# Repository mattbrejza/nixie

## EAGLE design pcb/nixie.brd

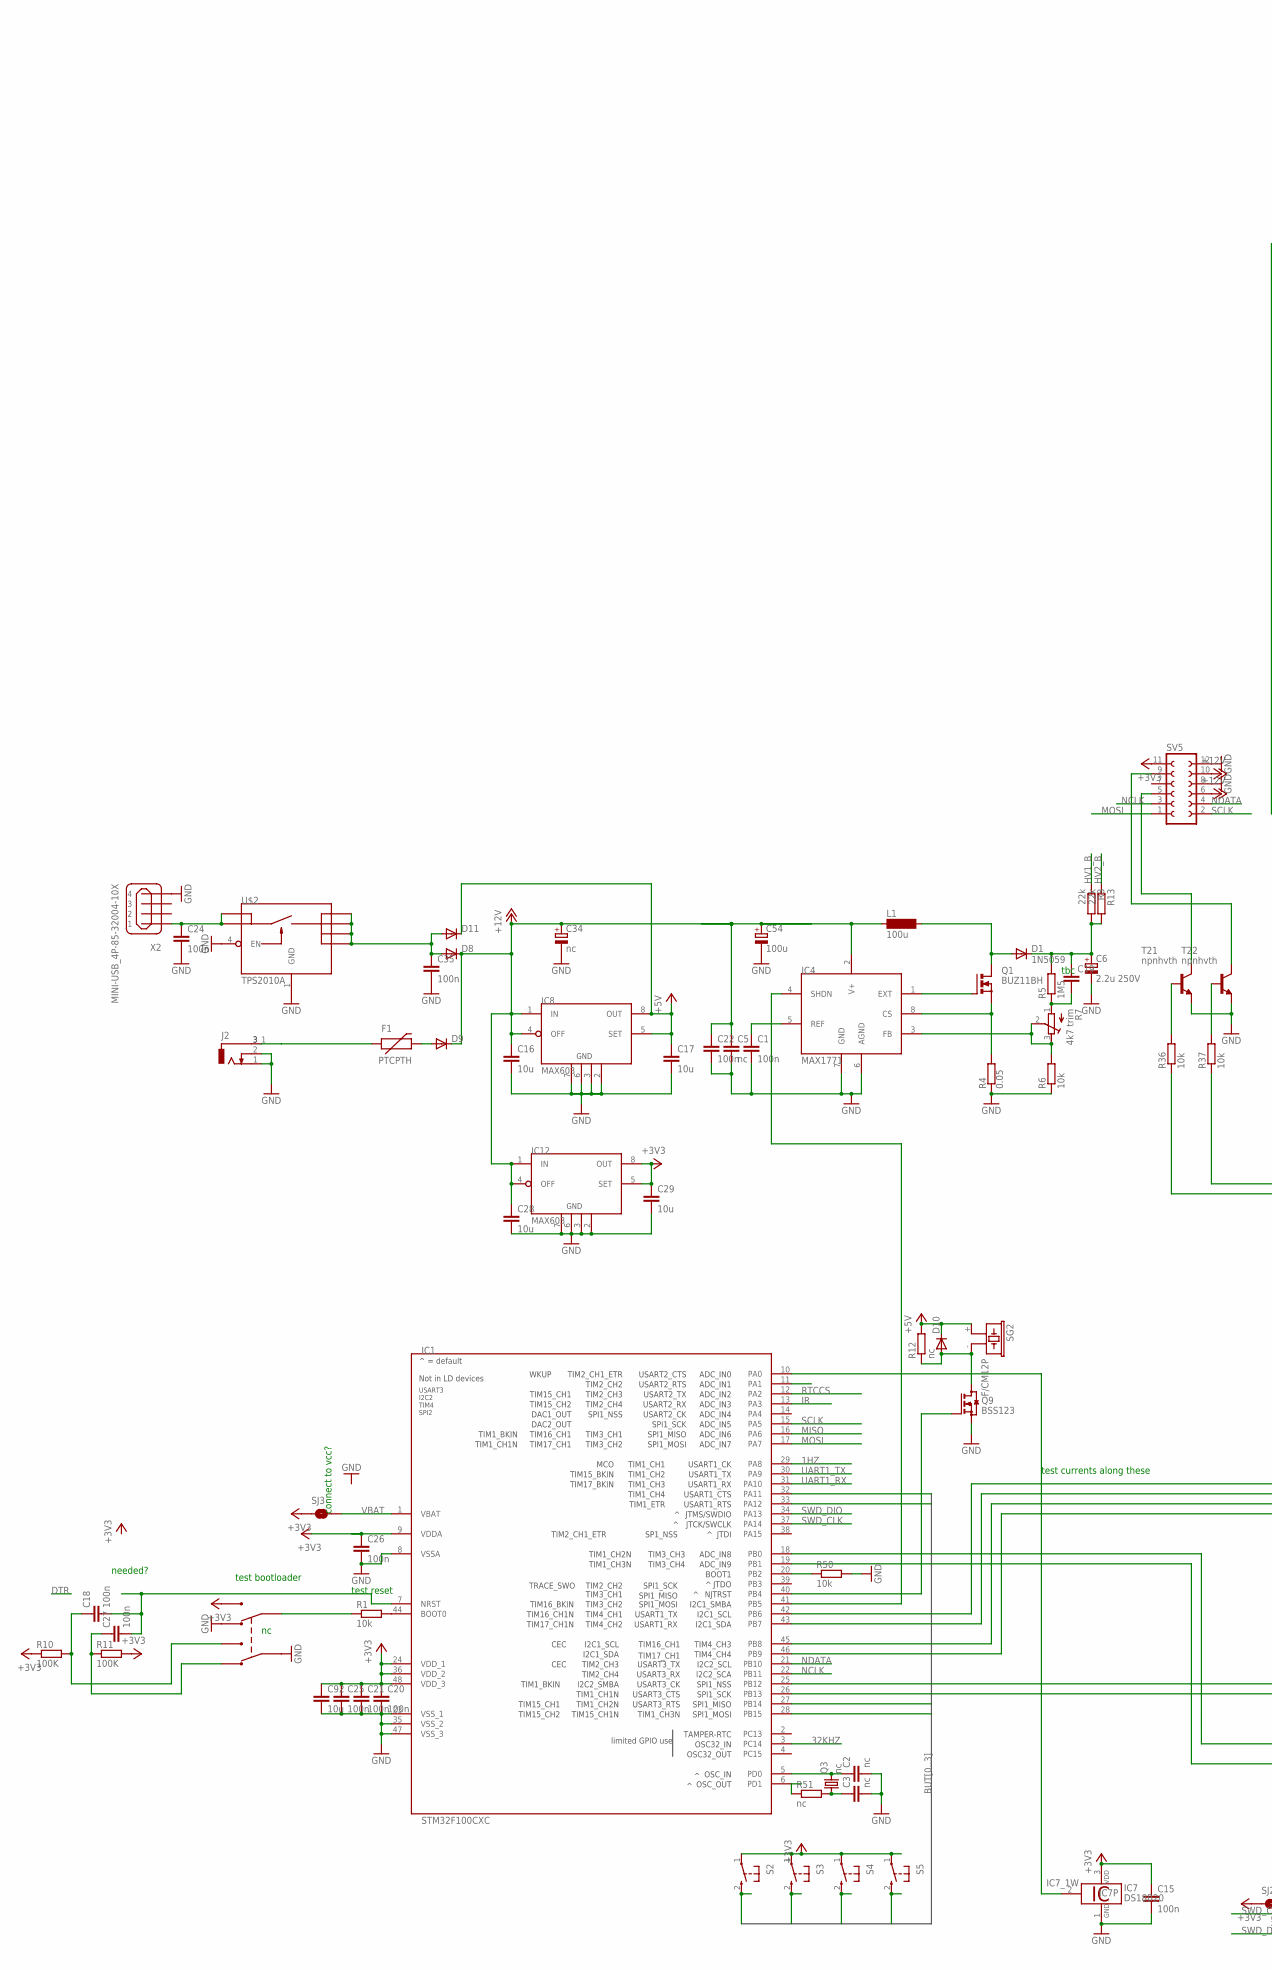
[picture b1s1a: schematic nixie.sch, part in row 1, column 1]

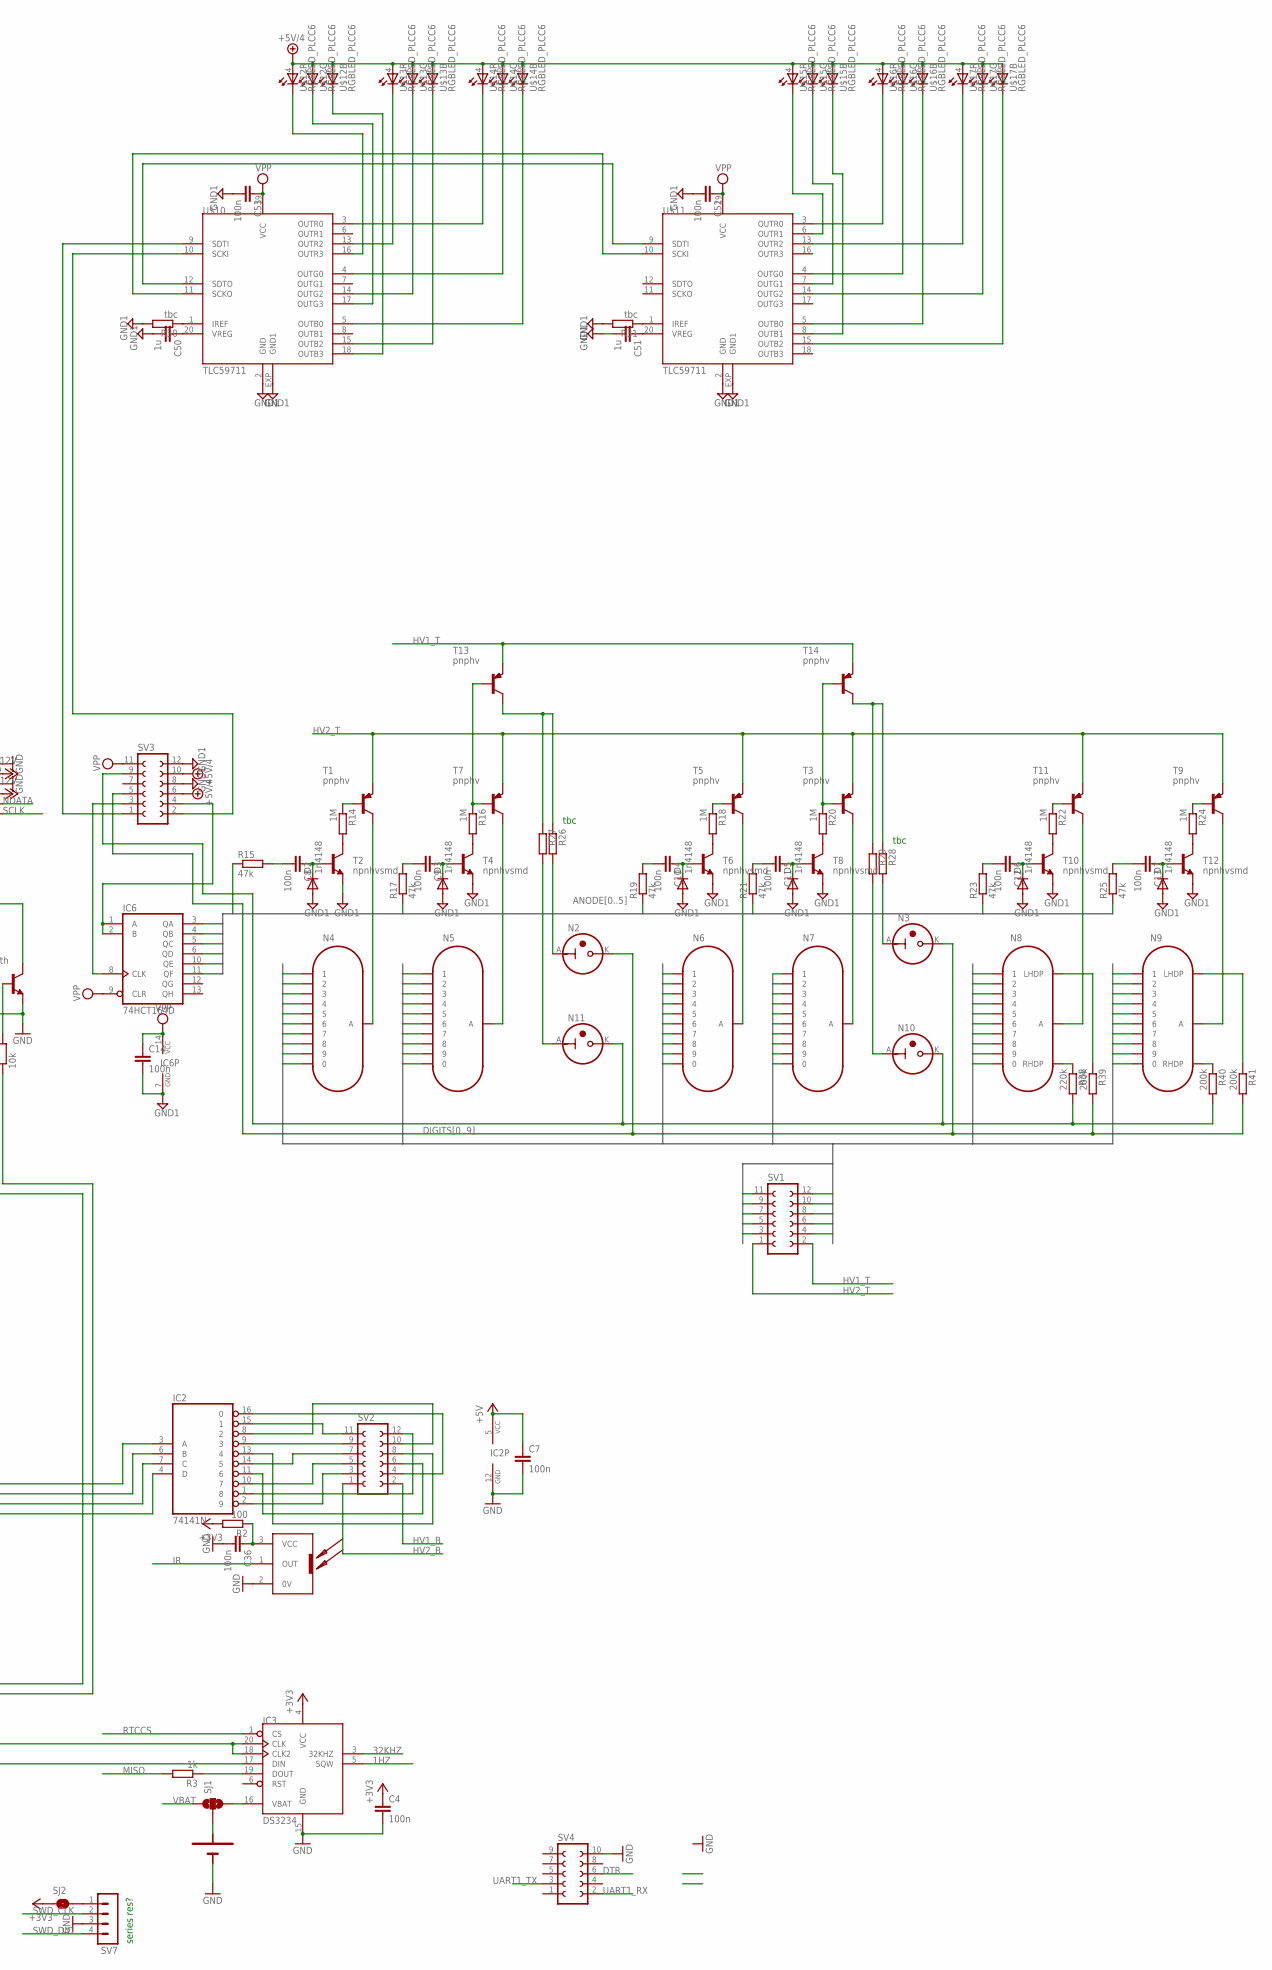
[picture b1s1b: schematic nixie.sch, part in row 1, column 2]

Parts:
BAT1: 2032; COIN
C1, C4, C7, C8, C9, C10, C11, C12, C13, C14, C15, C18, C20, C21, C22, C24, C25, C26, C27, C35, C36, C52, C53: 100n; C0603
C2, C3, C5: nc; C0603
C6: 2.2u 250V; E2,5-6
C16, C17, C28, C29, C92: 10u; C0603
C19: C-EUC0603; C0603
C34: nc; SMC_C
C50, C51: 1u; C0603
C54: 100u; E2,5-6
D1: 1N5059; C1702-05
D2, D3, D4, D5, D6, D7: 1n4148; SOD-323
D8, D9, D10, D11: DIODE-SOD123; SOD123
F1: PTCPTH; PTC
IC1: STM32F100CXC; SQFP-S-7X7-48
IC2: 74141N; DIL16
IC3: DS3234; SO20W
IC4: MAX1771; SO08
IC6: 74HCT164D; SO14
IC7: DS18B20; TO92-
IC8, IC12: MAX603; SO08
J2: DCJ0303SMD; SMD_JACK
L1: 100u; BS11
N2, N3, N10, N11: IN-3
N4, N5, N6, N7: IN-8
N8, N9: IN-16
Q1: BUZ11BH; TO220BH
Q3: nc; CTS406
Q9: BSS123; SOT23
R1, R6, R36, R37, R50: 10k; R0603
R2: 100; R0603
R3: 1k; R0603
R4: 0.05; SMS-WAV
R5: 1M5; R0603
R7: 4k7 trim; RTRIM3314J
R8, R13: 22k; R0805
R10, R11: 100K; R0603
R12, R51: nc; R0603
R14, R16, R18, R20, R22, R24: 1M; R0603
R15, R17, R19, R21, R23, R25: 47k; R0603
R26, R27, R28, R29: R-EU_R0603; R0603
R30, R31: tbc; R0603
R38: 220k; R0603
R39, R40, R41: 200k; R0603
S2, S3, S4, S5: TAC_SWITCH; TACTSIDE
SG2: F/CM12P
SJ1: SOLDERJUMPER_2WAYS; SJ_3
SJ2, SJ3: SOLDERJUMPERNO; SJ_2S-NO
SV1, SV2, SV3, SV5: FE06-2
SV4: FE05-2WED; EDGE_10
SV7: MA04-1E; EDGE_4
T1, T3, T5, T7, T9, T11, T13, T14: pnphv; SOT23-BEC
T2, T4, T6, T8, T10, T12: npnhvsmd; SOT23-3
T21, T22: npnhvth; TO92-EBC
U$1: IRREC
U$2: TPS2010A; SO-08
U$3: DPDTSLIDE
U$10, U$11: TLC59711; HTSSOP20PWP
U$12, U$13, U$14, U$15, U$16, U$17: RGBLED_PLCC6; PLCC6
X2: MINI-USB_4P-85-32004-10X; 85-32004-10X

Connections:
1HZ: IC1.29 (PA8), IC3.5 (SQW)
32KHZ: IC1.3 (PC14), IC3.3 (32KHZ)
+3V3: C4.1, C15.1, C20.1, C21.1, C25.1, C26.1, C29.1, C92.1, IC1.9 (VDDA), IC1.24 (VDD_1), IC1.36 (VDD_2), IC1.48 (VDD_3), IC3.4 (VCC), IC7.3 (VDD), IC12.5 (SET), IC12.8 (OUT), R2.2, R10.1, R11.2, S2.1, S3.1, S4.1, S5.1, SJ2.1, SJ3.1, SV5.11, U$3.2B (NO1)
+5V: C7.1, C17.1, D10.C, D11.C, IC2.5 (VCC), IC8.5 (SET), IC8.8 (OUT), R12.2, SG2.+ (1)
+5V/4: SV3.6, SV3.10, U$12.4 (A), U$12.5 (A), U$12.6 (A), U$13.4 (A), U$13.5 (A), U$13.6 (A), U$14.4 (A), U$14.5 (A), U$14.6 (A), U$15.4 (A), U$15.5 (A), U$15.6 (A), U$16.4 (A), U$16.5 (A), U$16.6 (A), U$17.4 (A), U$17.5 (A), U$17.6 (A)
+12V: C5.1, C16.1, C22.1, C28.1, C34.+, C54.+, D8.C, D9.C, IC4.2 (V+), IC8.1 (IN), IC8.4 (OFF), IC12.1 (IN), IC12.4 (OFF), L1.1, SV5.6, SV5.10
ANODE0: IC6.3 (QA), R15.1
ANODE1: IC6.4 (QB), R17.1
ANODE2: IC6.5 (QC), R19.1
ANODE3: IC6.6 (QD), R21.1
ANODE4: IC6.10 (QE), R23.1
ANODE5: IC6.11 (QF), R25.1
BUT0: IC1.32 (PA11), S5.2
BUT1: IC1.33 (PA12), S2.2
BUT2: IC1.28 (PB15), S4.2
BUT3: IC1.27 (PB14), S3.2
DIGITS0: N4.0, N5.0, N6.0, N7.0, N8.0, N9.0, SV1.3
DIGITS1: N4.1, N5.1, N6.1, N7.1, N8.1, N9.1, SV1.12
DIGITS2: N4.2, N5.2, N6.2, N7.2, N8.2, N9.2, SV1.5
DIGITS3: N4.3, N5.3, N6.3, N7.3, N8.3, N9.3, SV1.6
DIGITS4: N4.4, N5.4, N6.4, N7.4, N8.4, N9.4, SV1.7
DIGITS5: N4.5, N5.5, N6.5, N7.5, N8.5, N9.5, SV1.8
DIGITS6: N4.6, N5.6, N6.6, N7.6, N8.6, N9.6, SV1.9
DIGITS7: N4.7, N5.7, N6.7, N7.7, N8.7, N9.7, SV1.10
DIGITS8: N4.8, N5.8, N6.8, N7.8, N8.8, N9.8, SV1.11
DIGITS9: N4.9, N5.9, N6.9, N7.9, N8.9, N9.9, SV1.4
DTR: SV4.6
GND: BAT1.-, C1.2, C2.2, C3.2, C4.2, C5.2, C6.-, C7.2, C15.2, C16.2, C17.2, C20.2, C21.2, C22.2, C24.2, C25.2, C26.2, C28.2, C29.2, C34.-, C35.2, C36.2, C54.-, C92.2, IC1.8 (VSSA), IC1.23 (VSS_1), IC1.35 (VSS_2), IC1.47 (VSS_3), IC2.12 (GND), IC3.15 (GND), IC4.6 (AGND), IC4.7 (GND), IC7.1 (GND), IC8.2 (GND4), IC8.3 (GND3), IC8.6 (GND2), IC8.7 (GND1), IC12.2 (GND4), IC12.3 (GND3), IC12.7 (GND1), J2.1, J2.2, Q9.2 (S), R4.2, R6.1, R50.2, SV4.10, SV5.8, SV5.12, SV7.3, T21.E, T22.E, U$1.2 (0V), U$2.1 (GND), U$2.4 (EN), U$3.1X (COM0), U$3.2A (NC1), X2.4
GND1: C14.2, C50.2, C51.2, C52.2, C53.2, D2.2 (A), D3.2 (A), D4.2 (A), D5.2 (A), D6.2 (A), D7.2 (A), IC6.7 (GND), R30.2, R31.2, SV3.8, SV3.12, T2.2 (E), T4.2 (E), T6.2 (E), T8.2 (E), T10.2 (E), T12.2 (E), U$10.2 (GND), U$10.EXP (GND1), U$11.2 (GND), U$11.EXP (GND1)
GND2: IC12.6 (GND2)
HV1_B: R8.1, SV2.2
HV1_T: SV1.2, T13.E, T14.E
HV2_B: R13.1, SV2.1
HV2_T: SV1.1, T1.E, T3.E, T5.E, T7.E, T9.E, T11.E
IR: IC1.13 (PA3), U$1.1 (OUT)
LED5: SV3.2, U$10.10 (SCKI)
MISO: IC1.16 (PA6), R3.2
MOSI: IC1.17 (PA7), SV5.1
unnamed: F1.P$1 (1), J2.3, J2.3_1 (4)
unnamed: IC6.1 (A), IC6.2 (B), SV3.4
unnamed: BAT1.+, SJ1.2
unnamed: IC1.25 (PB12), R36.1
unnamed: IC3.19 (DOUT), R3.1
unnamed: IC1.42 (PB6), IC2.3 (A)
unnamed: IC3.16 (VBAT), SJ1.3
unnamed: IC1.19 (PB1), IC3.17 (DIN)
unnamed: IC1.18 (PB0), IC3.18 (CLK2), IC3.20 (CLK)
unnamed: IC1.43 (PB7), IC2.6 (B)
unnamed: IC1.45 (PB8), IC2.7 (C)
unnamed: IC1.46 (PB9), IC2.4 (D)
unnamed: IC4.1 (EXT), Q1.G
unnamed: IC4.8 (CS), Q1.S, R4.1
unnamed: D1.A, L1.2, Q1.D
unnamed: N3.A, R28.2
unnamed: C1.1, IC4.5 (REF)
unnamed: R14.2, T2.3 (C)
unnamed: SV3.1, U$10.9 (SDTI)
unnamed: C19.2, R5.1, R7.1 (E)
unnamed: IC4.3 (FB), R6.2, R7.2 (S), R7.3 (A)
unnamed: R14.1, T1.B
unnamed: C2.1, IC1.5 (PD0), Q3.3 (2)
unnamed: IC1.44 (BOOT0), R1.2
unnamed: N4.A, T1.C
unnamed: C6.+, C19.1, D1.C, R5.2, R8.2, R13.2
unnamed: C13.1, D7.1 (C), T12.1 (B)
unnamed: N5.A, T7.C
unnamed: R16.2, T4.3 (C)
unnamed: R16.1, T7.B, T13.B
unnamed: C13.2, R25.2
unnamed: N6.A, T5.C
unnamed: R18.2, T6.3 (C)
unnamed: R18.1, T5.B
unnamed: C12.1, D6.1 (C), T10.1 (B)
unnamed: R28.1, R29.1, T14.C
unnamed: R20.2, T8.3 (C)
unnamed: R20.1, T3.B, T14.B
unnamed: C12.2, R23.2
unnamed: N8.A, T11.C
unnamed: R22.2, T10.3 (C)
unnamed: R22.1, T11.B
unnamed: C11.1, D5.1 (C), T8.1 (B)
unnamed: N9.A, T9.C
unnamed: R24.2, T12.3 (C)
unnamed: R24.1, T9.B
unnamed: C11.2, R21.2
unnamed: IC1.6 (PD1), R51.1
unnamed: D9.A, F1.P$2 (2)
unnamed: SJ2.2, SV7.1
unnamed: IC1.40 (PB4), Q9.1 (G)
unnamed: N2.A, R26.2
unnamed: N11.A, R27.2
unnamed: D10.A, Q9.3 (D), R12.1, SG2.- (2)
unnamed: N10.A, R29.2
unnamed: N10.K, N11.K, R38.2, R40.2, SV3.9
unnamed: C24.1, U$2.2 (IN1), U$2.3 (IN2), X2.1
unnamed: R37.2, T22.B
unnamed: R36.2, T21.B
unnamed: C18.2, C27.2, IC1.7 (NRST)
unnamed: C35.1, D8.A, D11.A, U$2.5 (OUT1), U$2.6 (OUT2), U$2.7 (OUT3), U$2.8 (OUT4)
unnamed: C27.1, R11.1, U$3.1A (NC0)
unnamed: C18.1, R10.2, U$3.1B (NO0)
unnamed: IC1.26 (PB13), R37.1
unnamed: C10.1, D4.1 (C), T6.1 (B)
unnamed: C10.2, R19.2
unnamed: C9.1, D3.1 (C), T4.1 (B)
unnamed: C9.2, R17.2
unnamed: C8.1, D2.1 (C), T2.1 (B)
unnamed: C8.2, R15.2
unnamed: N8.RHDP, R38.1
unnamed: N8.LHDP, R39.1
unnamed: N9.RHDP, R40.1
unnamed: N9.LHDP, R41.1
unnamed: N2.K, N3.K, R39.2, R41.2, SV3.5
unnamed: IC1.10 (PA0), IC7.2 (1W)
unnamed: R26.1, R27.1, T13.C
unnamed: IC2.16 (0), SV2.4
unnamed: N7.A, T3.C
unnamed: IC2.15 (1), SV2.11
unnamed: IC2.9 (3), SV2.9
unnamed: IC2.14 (5), SV2.7
unnamed: IC2.10 (7), SV2.5
unnamed: IC2.8 (2), SV2.10
unnamed: IC2.2 (9), SV2.3
unnamed: IC2.1 (8), SV2.12
unnamed: IC2.11 (6), SV2.6
unnamed: IC2.13 (4), SV2.8
unnamed: IC6.8 (CLK), SV3.3
unnamed: SV5.5, T21.C
unnamed: SV5.9, T22.C
unnamed: U$10.16 (OUTR3), U$12.3 (B)
unnamed: U$10.13 (OUTR2), U$13.3 (B)
unnamed: U$10.3 (OUTR0), U$14.3 (B)
unnamed: U$10.17 (OUTG3), U$12.2 (B)
unnamed: U$10.14 (OUTG2), U$13.2 (B)
unnamed: IC1.41 (PB5), IC4.4 (SHDN)
unnamed: U$10.4 (OUTG0), U$14.2 (B)
unnamed: C36.1, R2.1, U$1.3 (VCC)
unnamed: U$10.18 (OUTB3), U$12.1 (B)
unnamed: U$10.15 (OUTB2), U$13.1 (B)
unnamed: U$10.5 (OUTB0), U$14.1 (B)
unnamed: U$11.6 (OUTR1), U$15.3 (B)
unnamed: U$11.3 (OUTR0), U$16.3 (B)
unnamed: U$11.13 (OUTR2), U$17.3 (B)
unnamed: U$11.7 (OUTG1), U$15.2 (B)
unnamed: U$11.4 (OUTG0), U$16.2 (B)
unnamed: U$11.14 (OUTG2), U$17.2 (B)
unnamed: U$11.8 (OUTB1), U$15.1 (B)
unnamed: U$11.5 (OUTB0), U$16.1 (B)
unnamed: U$11.15 (OUTB2), U$17.1 (B)
unnamed: C50.1, U$10.20 (VREG)
unnamed: R30.1, U$10.1 (IREF)
unnamed: C51.1, U$11.20 (VREG)
unnamed: R31.1, U$11.1 (IREF)
unnamed: U$10.12 (SDTO), U$11.9 (SDTI)
unnamed: U$10.11 (SCKO), U$11.10 (SCKI)
unnamed: R1.1, U$3.2X (COM1)
unnamed: IC1.20 (PB2), R50.1
unnamed: C3.1, Q3.1, R51.2
NCLK: IC1.22 (PB11), SV5.3
NDATA: IC1.21 (PB10), SV5.4
RTCCS: IC1.12 (PA2), IC3.1 (CS)
SCLK: IC1.15 (PA5), SV5.2
SWD_CLK: IC1.37 (PA14), SV7.2
SWD_DIO: IC1.34 (PA13), SV7.4
UART1_RX: IC1.31 (PA10), SV4.2
UART1_TX: IC1.30 (PA9), SV4.3
VBAT: IC1.1 (VBAT), SJ1.1, SJ3.2
VPP: C14.1, C52.1, C53.1, IC6.9 (CLR), IC6.14 (VCC), SV3.11, U$10.19 (VCC), U$11.19 (VCC)

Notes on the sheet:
test currents along these
series res?
test bootloader
test reset
needed?
connect to vcc?
tbc

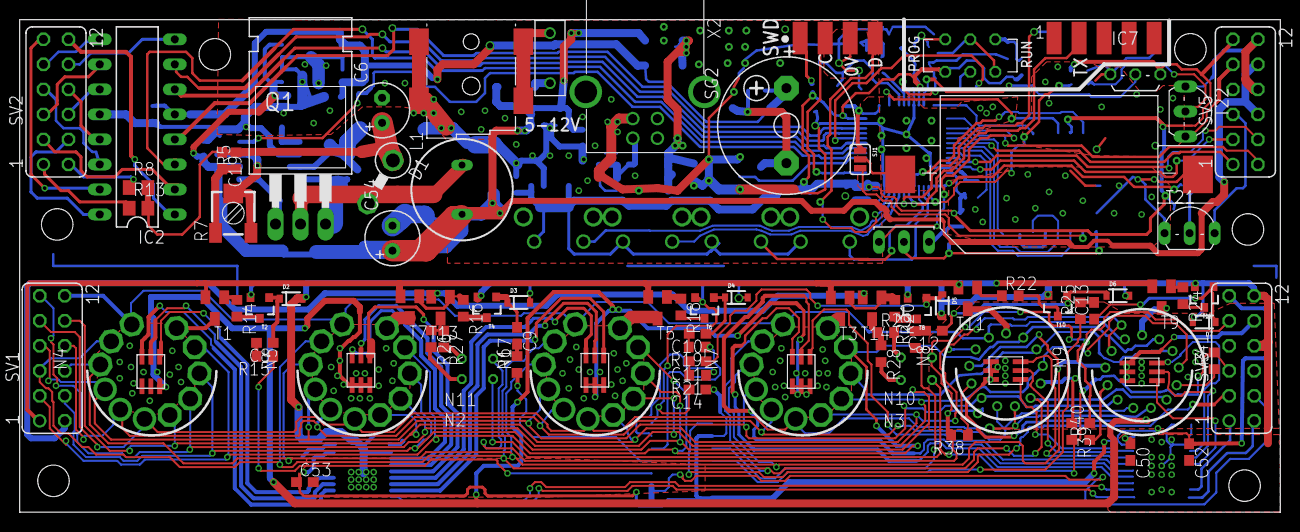
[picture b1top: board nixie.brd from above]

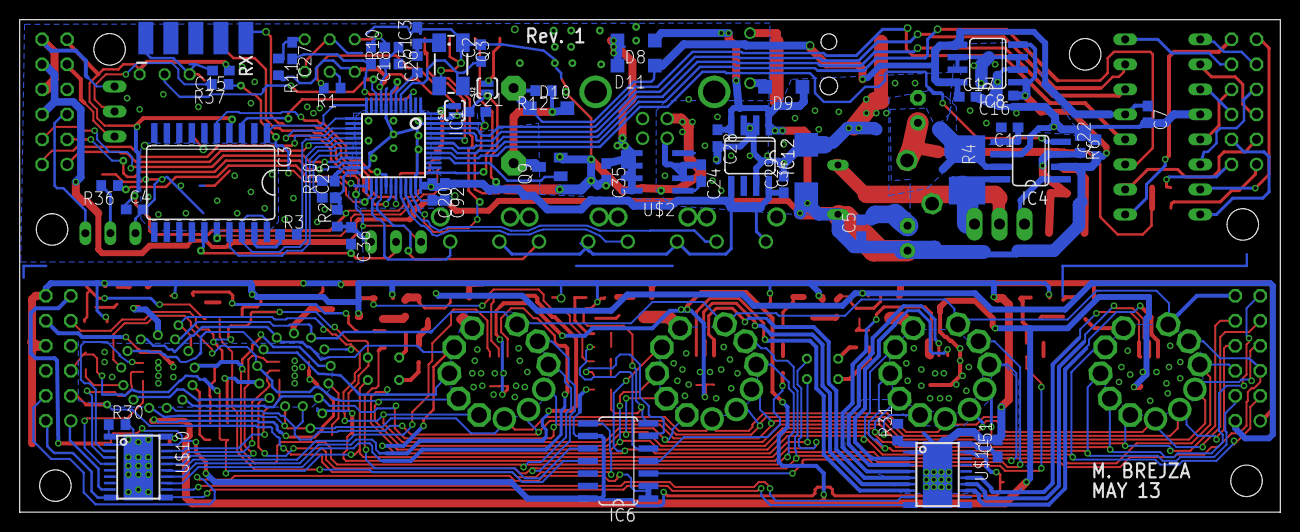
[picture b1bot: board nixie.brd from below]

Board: 2 copper layers, 128.0 x 50.0 mm, 153 parts (55 on the bottom side), 166 nets.

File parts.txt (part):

Partlist

Exported from nixie.sch at 04/05/2013 17:16:06

EAGLE Version 6.2.0 Copyright (c) 1988-2012 CadSoft

Assembly variant: 

Part     Value                    Device                   Package          Library                 Sheet

BAT1                              2032                     COIN             Mine                    1
C1       100n                     C-EUC0603                C0603            rcl                     1
C2       nc                       C-EUC0603                C0603            rcl                     1
C3       nc                       C-EUC0603                C0603            rcl                     1
C4       100n                     C-EUC0603                C0603            rcl                     1
C5       nc                       C-EUC0603                C0603            rcl                     1
C6       2.2u 250V                CPOL-EUE2.5-6            E2,5-6           rcl                     1
C7       100n                     C-EUC0603                C0603            rcl                     1
C8       100n                     C-EUC0603                C0603            rcl                     1
C9       100n                     C-EUC0603                C0603            rcl                     1
C10      100n                     C-EUC0603                C0603            rcl                     1
C11      100n                     C-EUC0603                C0603            rcl                     1
C12      100n                     C-EUC0603                C0603            rcl                     1
C13      100n                     C-EUC0603                C0603            rcl                     1
C14      100n                     C-EUC0603                C0603            rcl                     1
C15      100n                     C-EUC0603                C0603            rcl                     1
C16      10u                      C-EUC0603                C0603            rcl                     1
C17      10u                      C-EUC0603                C0603            rcl                     1
C18      100n                     C-EUC0603                C0603            rcl                     1
C19                               C-EUC0603                C0603            rcl                     1
C20      100n                     C-EUC0603                C0603            rcl                     1
C21      100n                     C-EUC0603                C0603            rcl                     1
C22      100n                     C-EUC0603                C0603            rcl                     1
C23      nc                       C-EUC0603                C0603            rcl                     1
C24      100n                     C-EUC1206                C1206            rcl                     1
C25      100n                     C-EUC0603                C0603            rcl                     1
C26      100n                     C-EUC0603                C0603            rcl                     1
C27      100n                     C-EUC0603                C0603            rcl                     1
C28      10u                      C-EUC0603                C0603            rcl                     1
C29      10u                      C-EUC0603                C0603            rcl                     1
C34      nc                       CPOL-EUSMCC              SMC_C            rcl                     1
C35      100n                     C-EUC0603                C0603            rcl                     1
C36      100n                     C-EUC0603                C0603            rcl                     1
C50      1u                       C-EUC0603                C0603            rcl                     1
C51      1u                       C-EUC0603                C0603            rcl                     1
C52      100n                     C-EUC0603                C0603            rcl                     1
C53      100n                     C-EUC0603                C0603            rcl                     1
C54      100u                     CPOL-EUE2.5-6            E2,5-6           rcl                     1
C92      10u                      C-EUC0603                C0603            rcl                     1
C93      100n                     C-EUC0603                C0603            rcl                     1
D1       1N5059                   DIODE-C1702-05           C1702-05         diode                   1
D2       1n4148                   DIODESOD                 SOD-323          SparkFun                1
D3       1n4148                   DIODESOD                 SOD-323          SparkFun                1
D4       1n4148                   DIODESOD                 SOD-323          SparkFun                1
D5       1n4148                   DIODESOD                 SOD-323          SparkFun                1
D6       1n4148                   DIODESOD                 SOD-323          SparkFun                1
D7       1n4148                   DIODESOD                 SOD-323          SparkFun                1
D8       CGRM4001-G               CGRM4001-G               SOD-123_MINI-SMA diode                   1
D9       CGRM4001-G               CGRM4001-G               SOD-123_MINI-SMA diode                   1
D10      CGRM4001-G               CGRM4001-G               SOD-123_MINI-SMA diode                   1
D11      CGRM4001-G               CGRM4001-G               SOD-123_MINI-SMA diode                   1
F1       PTCPTH                   PTCPTH                   PTC              SparkFun                1
IC1      STM32F100CXC             STM32F100CXC             SQFP-S-7X7-48    Mine                    1
IC2      74141N                   74141N                   DIL16            74xx-us                 1
IC3      DS3234                   DS3234                   SO20W            Mine                    1
IC4      MAX1771                  MAX1771                  SO08             Mine                    1
IC6      74HCT164D                74HCT164D                SO14             74xx-eu                 1
IC7      DS18B20                  DS18B20                  TO92-            1wire                   1
IC8      MAX603                   MAX603                   SO08             Mine                    1
IC12     MAX603                   MAX603                   SO08             Mine                    1
J2                                DCJ0303SMD               SMD_JACK         Mine                    1
L1       100u                     BS11                     BS11             inductor-neosid         1
L2                                WE-CBF_0805              0805             wuerth-elektronik       1
N2       IN-3                     IN-3                     IN-3             russian-nixies-mod      1
N3       IN-3                     IN-3                     IN-3             russian-nixies-mod      1
N4       IN-8                     IN-8                     IN-8             IN8                     1
N5       IN-8                     IN-8                     IN-8             IN8                     1
N6       IN-8                     IN-8                     IN-8             IN8                     1
N7       IN-8                     IN-8                     IN-8             IN8                     1
N8       IN-16                    IN-16                    IN-16            russian-nixies          1
N9       IN-16                    IN-16                    IN-16            russian-nixies          1
N10      IN-3                     IN-3                     IN-3             russian-nixies-mod      1
N11      IN-3                     IN-3                     IN-3             russian-nixies-mod      1
Q1       BUZ11BH                  BUZ11BH                  TO220BH          Mine                    1
Q3       nc                       CRYSTALCTS406            CTS406           crystal                 1
Q9       BSS123                   BSS123                   SOT23            transistor-small-signal 1
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
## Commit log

2013-04-04 moving stuff around
2013-04-16 some routing improvements. about to mess about with the inductor area a little
2013-04-16 finished moving inductor
2013-05-02 mostly silk screen stuff
2013-05-04 almost done
2013-05-07 just before merge
2013-05-07 deleted stuff for merging
2013-05-07 removing files after being moved somewhere else
2013-05-08 off for fab
2014-08-23 dma spi and leds working
2014-08-24 displays digits
2014-09-05 cleaning up
2015-01-24 still testing
2015-04-06 lots done
2015-04-25 fixed flicker due to 1Hz IRQ
2015-04-27 adding notes to sch
2015-10-24 done
2015-10-25 even more done
